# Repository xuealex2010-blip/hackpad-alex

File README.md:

# CADPAD

A Numberpad with navigation controls with a secondary macro layer. Made to improve my CAD experience.

## Navigation Knob

Featuring navigation accessibility especially for when entering numbers. 

The arrow key outputs give a tactile way to move around the numbers to correct mistakes on the same input device. The tab button also allows for quick navigation between text fields.

## See it in Action!

Here's a short demo video of some of the features, such as the Tap Dance, and Navigation Knob
[Video](https://www.youtube.com/watch?v=yww2Ed7qnjQ)

## PCB and Schematic Design

The Schematic and PCB can also be viewed HERE >>
https://kicanvas.org/?repo=https%3A%2F%2Fgithub.com%2Fxuealex2010-blip%2Fhackpad-alex%2Ftree%2Fmain%2FPCB

### Schematic Overview

The GPIO pins are optimized to support a larger 4x5 matrix, making this design able to be used for even more projects.

The encoder switch is wired into the matrix to reduce the pins used.

### PCB (GND Fill Hidden)

This design also makes use of 2 special hybrid footprints.

The **Hybrid Switch** footprint supports both MX style and Choc switches, making the design more customizable.

The **Hybrid Diode** which I actually created myself supports common SOD-123 and Through Hole 1N4148 diodes to make it fit the users choice.

### PCB Render

## Case Assembly
Using a sandwich mount for ease of assembly.

The case is also designed with a slight tilt to make the front lip lower to be more comfortable.

The advantage of 3D printing also means that if I want to use different keyswitches, the complex PCB can remain the same, the case can be further customized for that setup.

## Keymap

The layout for the Cadpad follows the common number arrangement of calculators, helping muscle memory carry over.

The `.` and `Enter` keys also utilize QMK's Tap Dance feature.

`.` When double clicked will register a backspace input, this was chosen since a double decimal is not used.

`Enter` acts as the layer modifier when held, accessing the extra function buttons set for macros, as well as common volume controls with the encoder.

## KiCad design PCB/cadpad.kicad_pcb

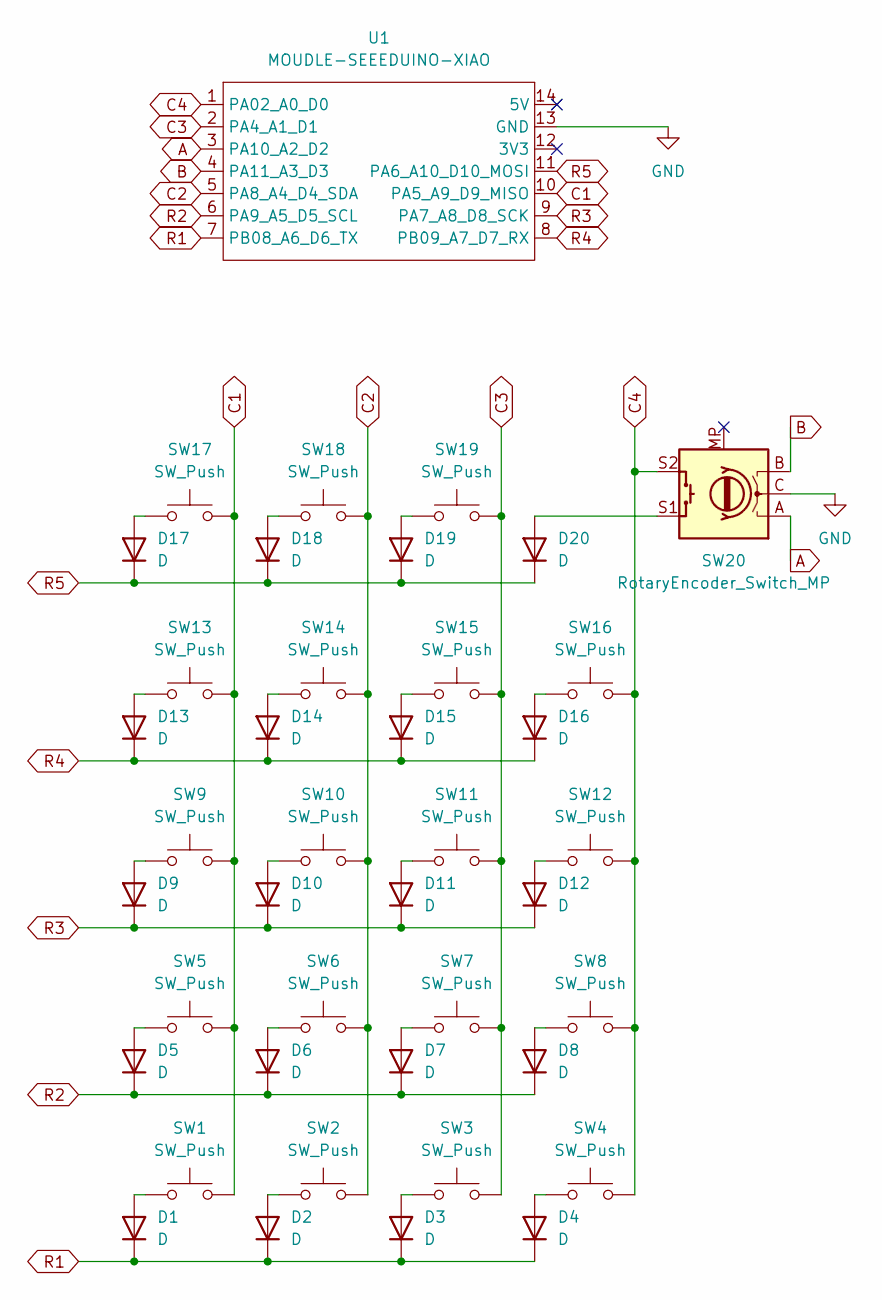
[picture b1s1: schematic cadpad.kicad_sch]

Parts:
D1, D2, D3, D4, D5, D6, D7, D8, D9, D10, D11, D12, D13, D14, D15, D16, D17, D18, D19, D20: D; D_Combo
SW1, SW2, SW3, SW4, SW5, SW6, SW7, SW8, SW9, SW10, SW11, SW12, SW13, SW14, SW15, SW16, SW17, SW19: SW_Push; SW_Combo_MX_Choc
SW18: SW_Push; SW_Combo_MX_Choc(NoPCBpin)
SW20: RotaryEncoder_Switch_MP; ROT_Alps_EC11E-Switch
U1: MOUDLE-SEEEDUINO-XIAO; XIAO-Generic-Hybrid-14P-2.54-21X17.8MM

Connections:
A: SW20.A, U1.3 (PA10_A2_D2)
B: SW20.B, U1.4 (PA11_A3_D3)
C1: SW1.2, SW5.2, SW9.2, SW13.2, SW17.2, U1.10 (PA5_A9_D9_MISO)
C2: SW2.2, SW6.2, SW10.2, SW14.2, SW18.2, U1.5 (PA8_A4_D4_SDA)
C3: SW3.2, SW7.2, SW11.2, SW15.2, SW19.2, U1.2 (PA4_A1_D1)
C4: SW4.2, SW8.2, SW12.2, SW16.2, SW20.S2, U1.1 (PA02_A0_D0)
GND: SW20.C, U1.13 (GND)
unnamed: D1.2 (A), SW1.1
unnamed: D2.2 (A), SW2.1
unnamed: D3.2 (A), SW3.1
unnamed: D4.2 (A), SW4.1
unnamed: D5.2 (A), SW5.1
unnamed: D6.2 (A), SW6.1
unnamed: D7.2 (A), SW7.1
unnamed: D8.2 (A), SW8.1
unnamed: D9.2 (A), SW9.1
unnamed: D10.2 (A), SW10.1
unnamed: D11.2 (A), SW11.1
unnamed: D12.2 (A), SW12.1
unnamed: D13.2 (A), SW13.1
unnamed: D14.2 (A), SW14.1
unnamed: D15.2 (A), SW15.1
unnamed: D16.2 (A), SW16.1
unnamed: D17.2 (A), SW17.1
unnamed: D18.2 (A), SW18.1
unnamed: D19.2 (A), SW19.1
unnamed: D20.2 (A), SW20.S1
R1: D1.1 (K), D2.1 (K), D3.1 (K), D4.1 (K), U1.7 (PB08_A6_D6_TX)
R2: D5.1 (K), D6.1 (K), D7.1 (K), D8.1 (K), U1.6 (PA9_A5_D5_SCL)
R3: D9.1 (K), D10.1 (K), D11.1 (K), D12.1 (K), U1.9 (PA7_A8_D8_SCK)
R4: D13.1 (K), D14.1 (K), D15.1 (K), D16.1 (K), U1.8 (PB09_A7_D7_RX)
R5: D17.1 (K), D18.1 (K), D19.1 (K), D20.1 (K), U1.11 (PA6_A10_D10_MOSI)

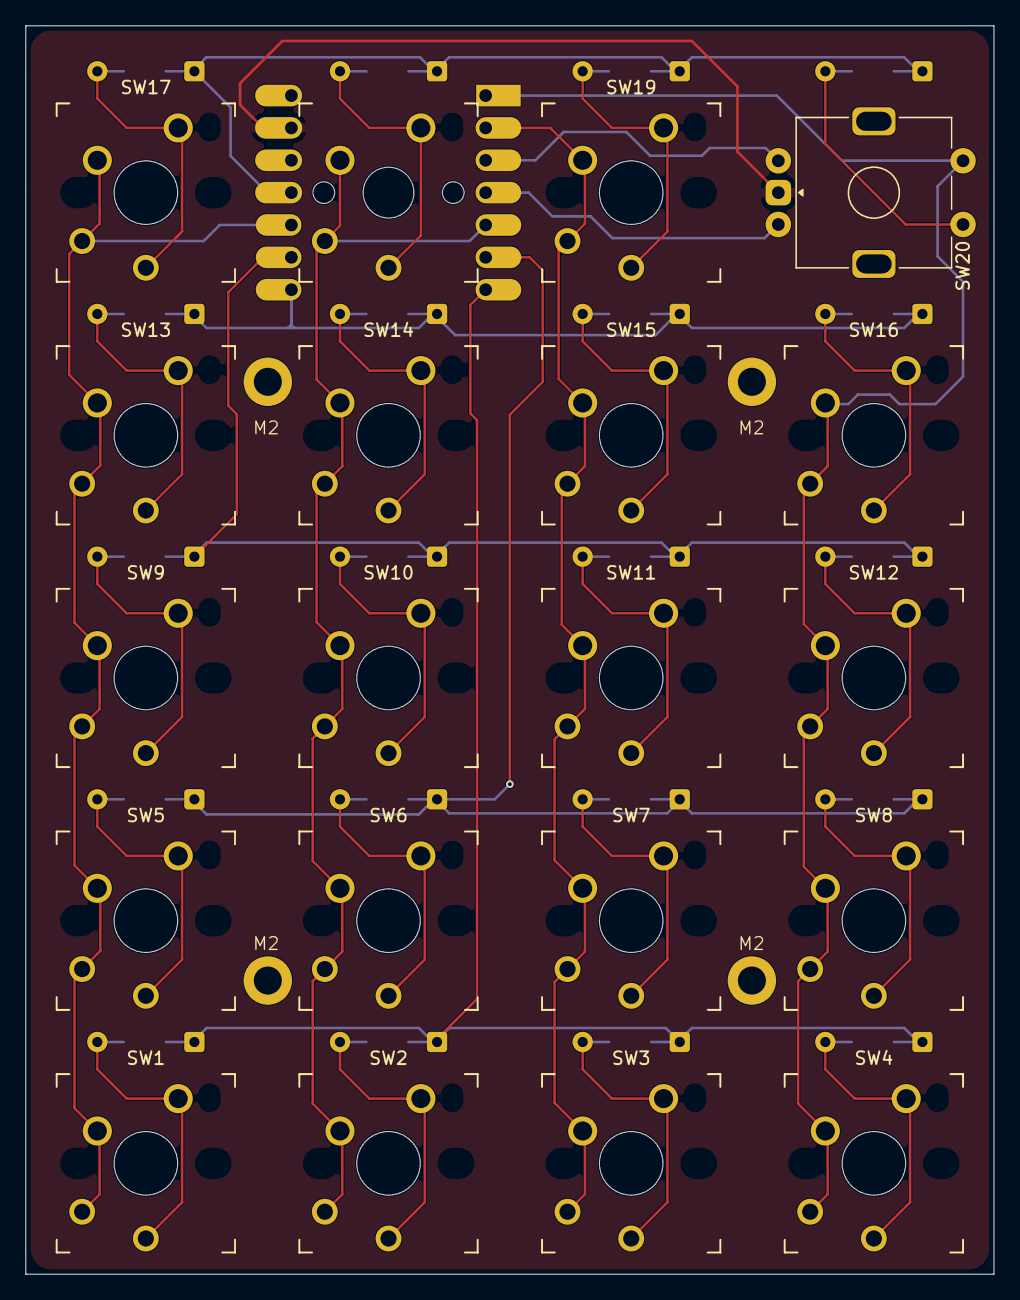
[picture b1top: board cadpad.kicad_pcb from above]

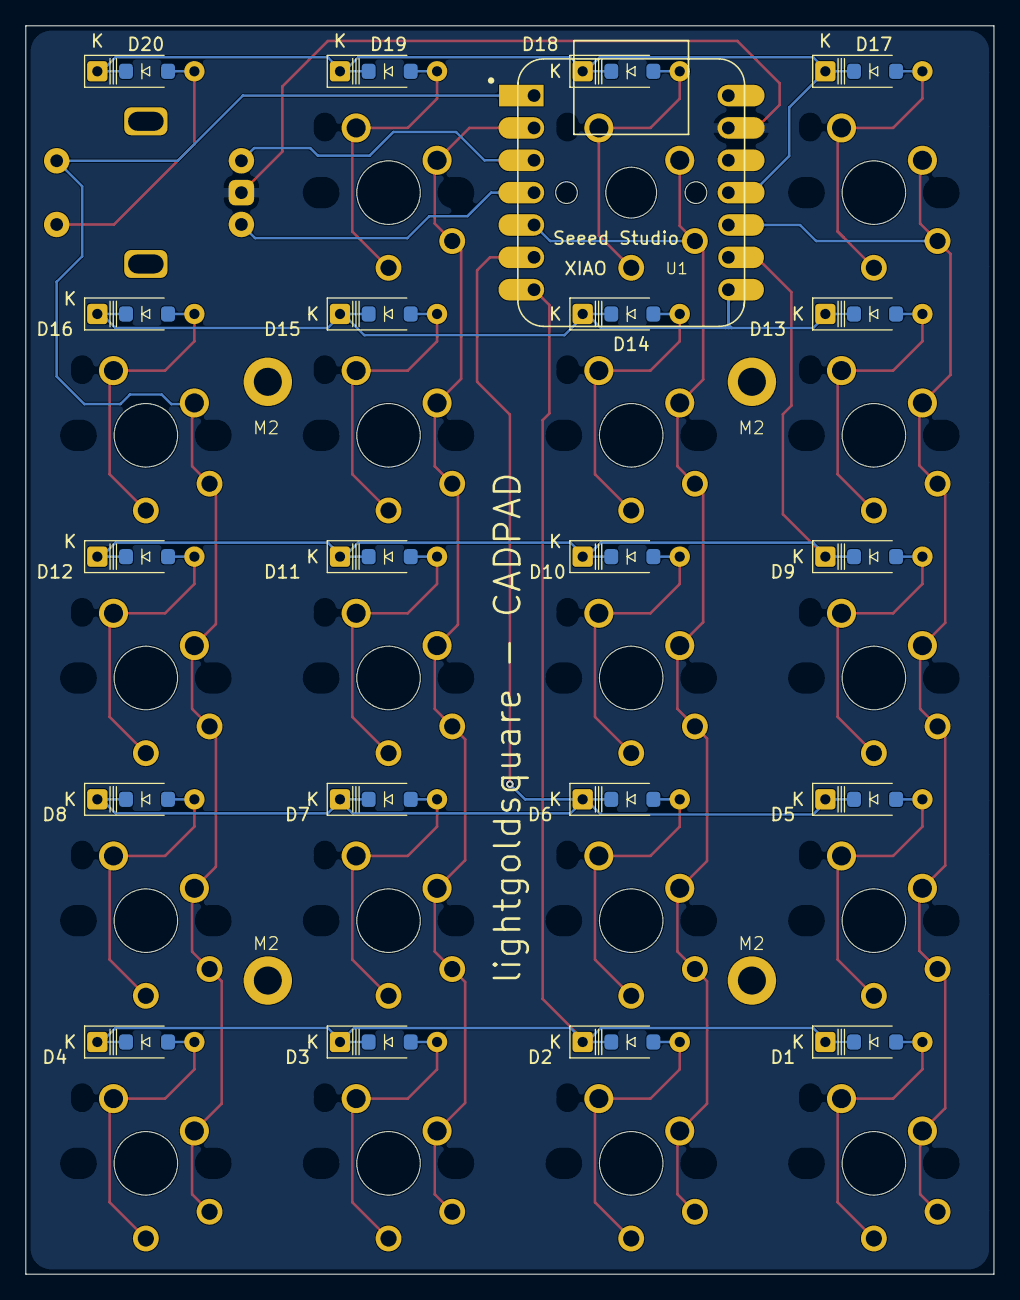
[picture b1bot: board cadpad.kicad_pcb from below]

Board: 2 copper layers, 76.0 x 98.0 mm, 45 parts (21 on the bottom side), 32 nets.

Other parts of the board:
M2, M2#2, M2#3, M2#4: MountingHole_2.2mm_M2_DIN965_Pad

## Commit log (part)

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2026-06-07 Create test
2026-06-07 Create .wakatime-project
